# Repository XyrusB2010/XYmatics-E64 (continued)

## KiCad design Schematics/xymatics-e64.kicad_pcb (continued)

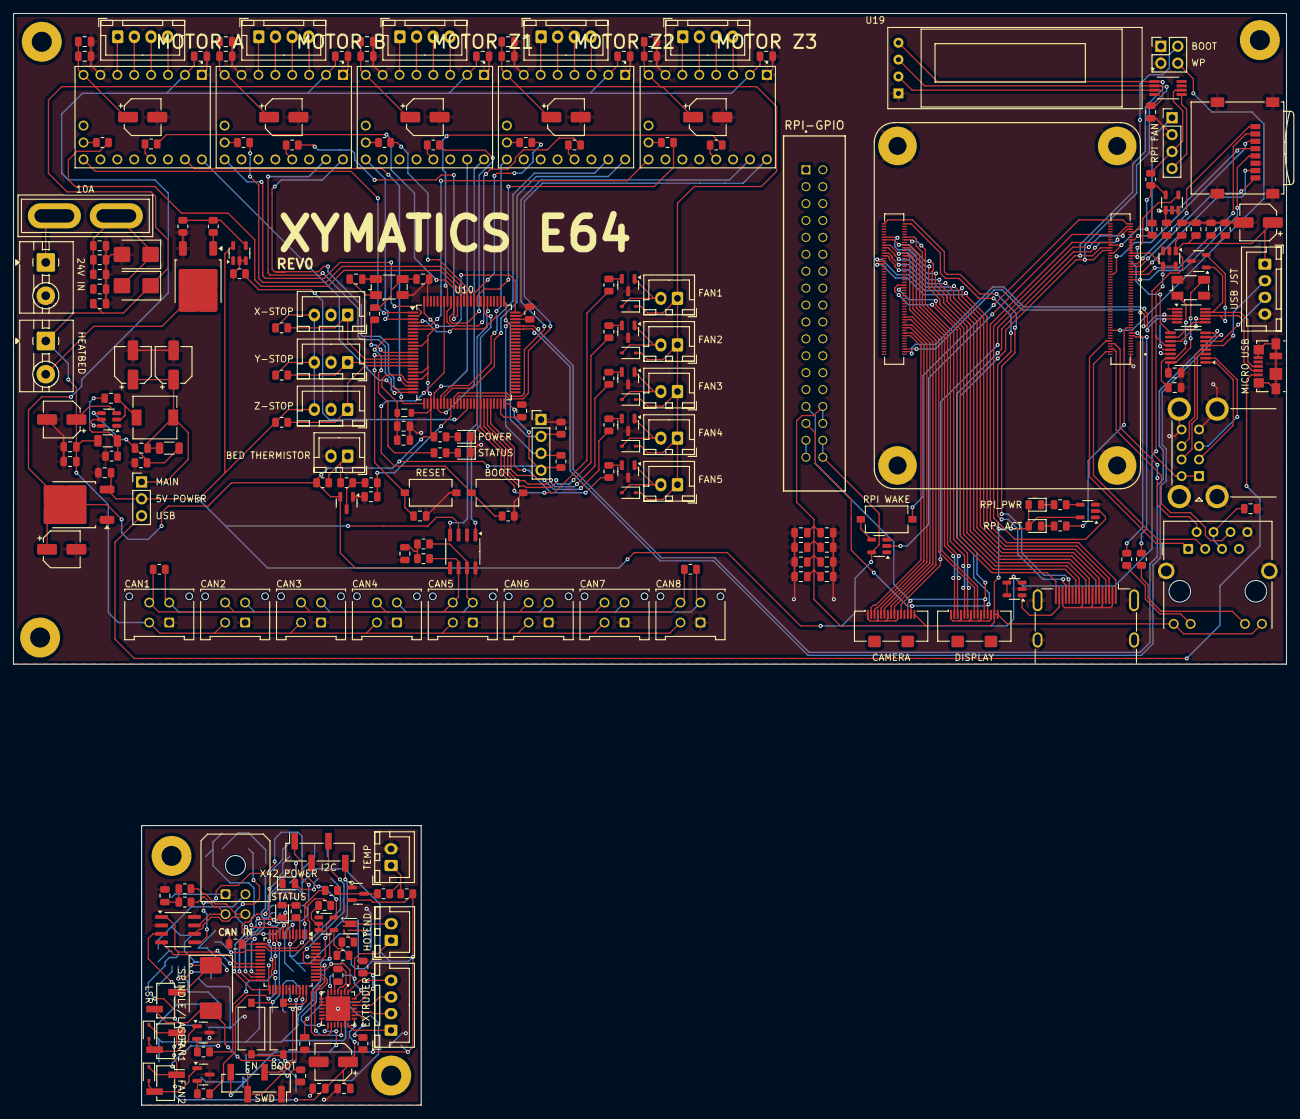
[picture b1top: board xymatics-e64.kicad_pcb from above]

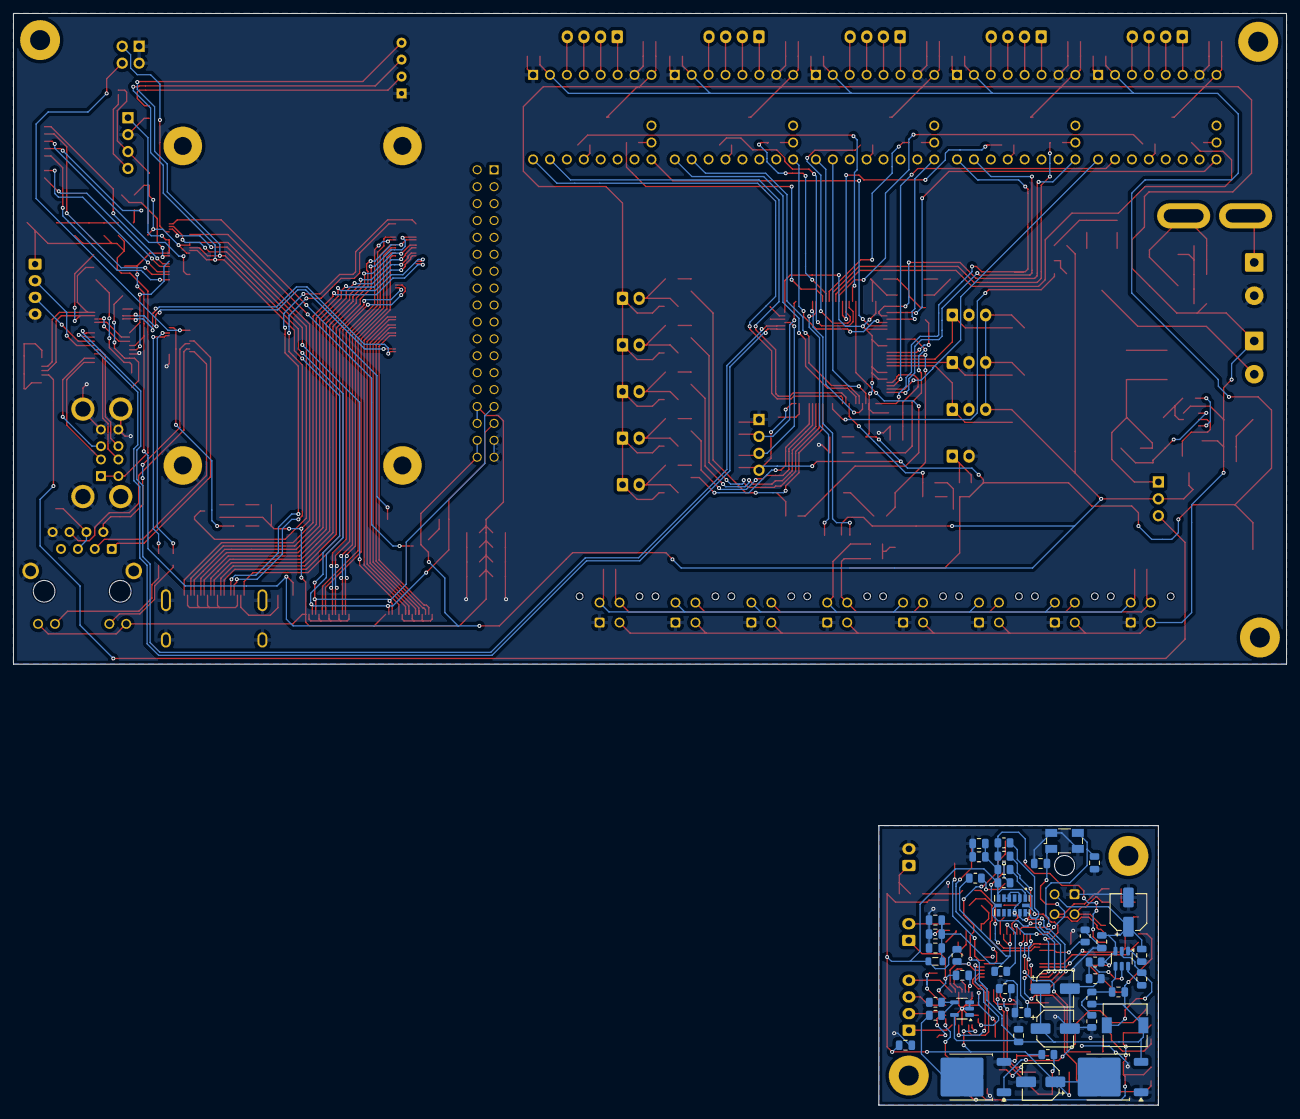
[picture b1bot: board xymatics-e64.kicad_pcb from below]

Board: 2 copper layers, 191.2 x 164.0 mm, 282 parts (43 on the bottom side), 275 nets.

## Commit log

2025-07-20 Create JOURNAL.md
    7/07/2025 - Begin PCB design
2025-07-20 Add xymatics-e64.kicad_sch
2025-07-20 Add cm4.kicad_sch
2025-07-20 Add xymatics-e64.pdf
2025-07-20 Update JOURNAL.md
    # 14/07/2025 - Finish STM32 schematic and begin X42 schematic
2025-07-20 Add x42.kicad_sch
2025-07-20 Update JOURNAL.md
    20/07/2025 - Finish X42 schematic
2025-07-20 Update Schematics
    Update CM4, X42, XYmatics-E64 schematics
2025-07-20 Update xymatics-e64.pdf
    Edited xymatics-e64.pdf
2025-07-23 Update JOURNAL.md
    23/07/2025 - Update on X42
2025-07-23 Update X42 schematics, Add project PCB
    Removed Neopixel and BLTouch breakouts from X42, added X42 PCB (unfinished)
2025-07-23 Update README.md
    Edit X42 Features, Add X42 PCB renders
2025-07-24 Update JOURNAL.md
    25/07/2025 - Finish X42 PCB
2025-07-24 Update X42 schematics, Update X42 PCB
    Removed X42 Endstops (re-add in next revision)
2025-08-03 Update JOURNAL.md
    31/07/2025 - E64 PCB complete
2025-08-03 Update E64 schematics
    Finish E64 PCB
2025-08-03 Add gerber files
2025-08-03 Update README.md
    Update PCB renders
